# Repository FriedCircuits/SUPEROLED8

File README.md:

# SUPEROLED8
Development board for ATmega32U4 complete with 128x64 OLED and 5 way navigation button. 

License: All source code and designs are released under 

Creative Commons By ShareAlike 

CC BY-SA

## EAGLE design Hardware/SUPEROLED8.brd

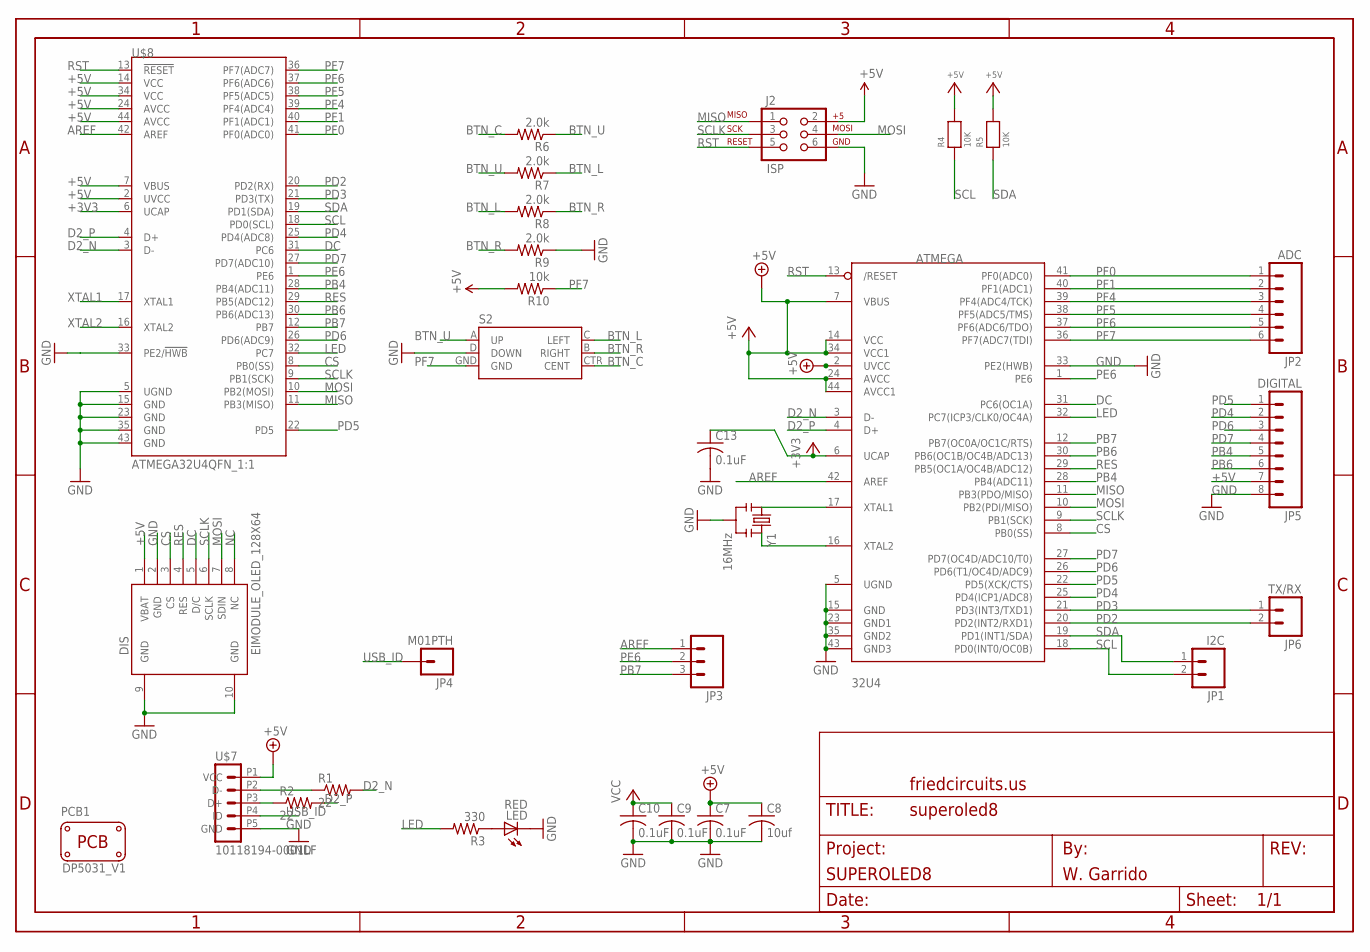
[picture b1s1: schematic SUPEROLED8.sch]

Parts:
32U4: ATMEGA; TQFP44
C7, C9, C10, C13: 0.1uF; C0805K
C8: 10uf; C0805K
DIS: EIMODULE_OLED_128X64
J2: ISP; 2X3_LOCK
JP1: I2C; 1X02_LOCK
JP2: ADC; 1X06_LOCK
JP3: M03LOCK; 1X03_LOCK
JP4: M01PTH; 1X01
JP5: DIGITAL; 1X08_LOCK
JP6: TX/RX; 1X02_LOCK
LED: RED; CHIPLED_0805
PCB1: PCB_DP_RECTANGLE-31X50; DP5031_V1
R1, R2: 22; R0805
R3: 330; R0805
R4, R5: 10K; 0805
R6, R7, R8, R9: 2.0k; 0603-RES
R10: 10k; 0603-RES
S2: JOYSTICK_MINI
U$1: FRAME_DINA4_L; FC_CREDIT
U$7: 10118194-0001LF
U$8: ATMEGA32U4QFN_1:1; QFN-44-NOPAD_1:1
Y1: 16MHz; RESONATOR-SMD

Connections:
+3V3: 32U4.6 (UCAP), C13.1, U$8.6 (UCAP)
+5V: 32U4.2 (UVCC), 32U4.7 (VBUS), 32U4.14 (VCC), 32U4.24 (AVCC), 32U4.34 (VCC1), 32U4.44 (AVCC1), C7.1, C8.1, C9.1, C10.1, DIS.1 (VBAT), J2.2, JP5.7, R4.2, R5.2, R10.2, U$7.P1 (VCC), U$8.2 (UVCC), U$8.7 (VBUS), U$8.14 (VCC), U$8.24 (AVCC), U$8.34 (VCC), U$8.44 (AVCC)
AREF: 32U4.42 (AREF), JP3.1, U$8.42 (AREF)
BTN_C: R6.2, S2.CTR (CENT)
BTN_L: R7.1, R8.2, S2.C (LEFT)
BTN_R: R8.1, R9.2, S2.B (RIGHT)
BTN_U: R6.1, R7.2, S2.A (UP)
CS: 32U4.8 (PB0(SS)), DIS.3 (CS), U$8.8 (PB0(SS))
D2_N: 32U4.3 (D-), R1.2, U$8.3 (D-)
D2_P: 32U4.4 (D+), R2.2, U$8.4 (D+)
DC: 32U4.31 (PC6(OC1A)), DIS.5 (D/C), U$8.31 (PC6)
GND: 32U4.5 (UGND), 32U4.15 (GND), 32U4.23 (GND1), 32U4.33 (PE2(HWB)), 32U4.35 (GND2), 32U4.43 (GND3), C7.2, C8.2, C9.2, C10.2, C13.2, DIS.2 (GND), DIS.9 (GND), DIS.10 (GND), J2.6, JP5.8, LED.C, R9.1, S2.D (DOWN), U$7.P5 (GND), U$8.5 (UGND), U$8.15 (GND), U$8.23 (GND), U$8.35 (GND), U$8.43 (GND), Y1.2
LED: 32U4.32 (PC7(ICP3/CLK0/OC4A)), R3.2, U$8.32 (PC7)
MISO: 32U4.11 (PB3(PDO/MISO)), J2.1, U$8.11 (PB3(MISO))
MOSI: 32U4.10 (PB2(PDI/MISO)), DIS.7 (SDIN), J2.4, U$8.10 (PB2(MOSI))
unnamed: LED.A, R3.1
NC: DIS.8 (NC)
PB4: 32U4.28 (PB4(ADC11)), JP5.5, U$8.28 (PB4(ADC11))
PB6: 32U4.30 (PB6(OC1B/OC4B/ADC13)), JP5.6, U$8.30 (PB6(ADC13))
PB7: 32U4.12 (PB7(OC0A/OC1C/RTS)), JP3.3, U$8.12 (PB7)
PD2: 32U4.20 (PD2(INT2/RXD1)), JP6.2, U$8.20 (PD2(RX))
PD3: 32U4.21 (PD3(INT3/TXD1)), JP6.1, U$8.21 (PD3(TX))
PD4: 32U4.25 (PD4(ICP1/ADC8)), JP5.2, U$8.25 (PD4(ADC8))
PD5: 32U4.22 (PD5(XCK/CTS)), JP5.1, U$8.22 (PD5)
PD6: 32U4.26 (PD6(T1/OC4D/ADC9)), JP5.3, U$8.26 (PD6(ADC9))
PD7: 32U4.27 (PD7(OC4D/ADC10/T0)), JP5.4, U$8.27 (PD7(ADC10))
PE6: 32U4.1 (PE6), JP3.2, U$8.1 (PE6)
PF0: 32U4.41 (PF0(ADC0)), JP2.1, U$8.41 (PF0(ADC0))
PF1: 32U4.40 (PF1(ADC1)), JP2.2, U$8.40 (PF1(ADC1))
PF4: 32U4.39 (PF4(ADC4/TCK)), JP2.3, U$8.39 (PF4(ADC4))
PF5: 32U4.38 (PF5(ADC5/TMS)), JP2.4, U$8.38 (PF5(ADC5))
PF6: 32U4.37 (PF6(ADC6/TDO)), JP2.5, U$8.37 (PF6(ADC6))
PF7: 32U4.36 (PF7(ADC7(TDI)), JP2.6, R10.1, S2.GND, U$8.36 (PF7(ADC7))
RES: 32U4.29 (PB5(OC1A/OC4B/ADC12)), DIS.4 (RES), U$8.29 (PB5(ADC12))
RST: 32U4.13 (/RESET), J2.5, U$8.13 (!RESET)
SCL: 32U4.18 (PD0(INT0/OC0B)), JP1.2, R4.1, U$8.18 (PD0(SCL))
SCLK: 32U4.9 (PB1(SCK)), DIS.6 (SCLK), J2.3, U$8.9 (PB1(SCK))
SDA: 32U4.19 (PD1(INT1/SDA)), JP1.1, R5.1, U$8.19 (PD1(SDA))
USB_C_N: R1.1, U$7.P2 (D-)
USB_C_P: R2.1, U$7.P3 (D+)
USB_ID: JP4.1, U$7.P4 (ID)
XTAL1: 32U4.17 (XTAL1), U$8.17 (XTAL1), Y1.1
XTAL2: 32U4.16 (XTAL2), U$8.16 (XTAL2), Y1.3

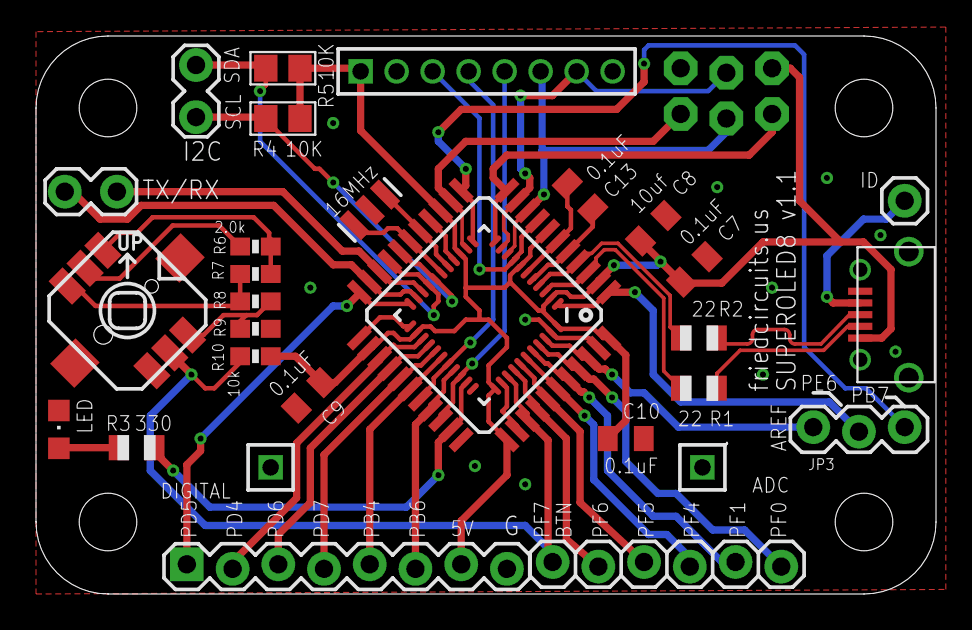
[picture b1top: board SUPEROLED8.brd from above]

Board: 2 copper layers, 50.0 x 31.0 mm, 31 parts (1 on the bottom side), 42 nets.

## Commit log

2016-04-21 Fixed comment header
2016-04-21 Added Analogbuttons submodule
2016-04-21 Added submodule for AnalogButtons
2016-04-21 Added images of hardware design files
2016-04-21 Larger board image file
2016-04-21 Larger board image
2016-04-23 Added license file
2016-05-30 Added 2nd demo
    Faster repeat rate without using library

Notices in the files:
parts and their libraries:
SparkFun-Connectors: Licensing: CC v3.0 Share-Alike You are welcome to use this library for commercial purposes.
SparkFun-Resistors: Licensing: Creative Commons ShareAlike 4.0 International - https://creativecommons.org/licenses/by-sa/4.0
